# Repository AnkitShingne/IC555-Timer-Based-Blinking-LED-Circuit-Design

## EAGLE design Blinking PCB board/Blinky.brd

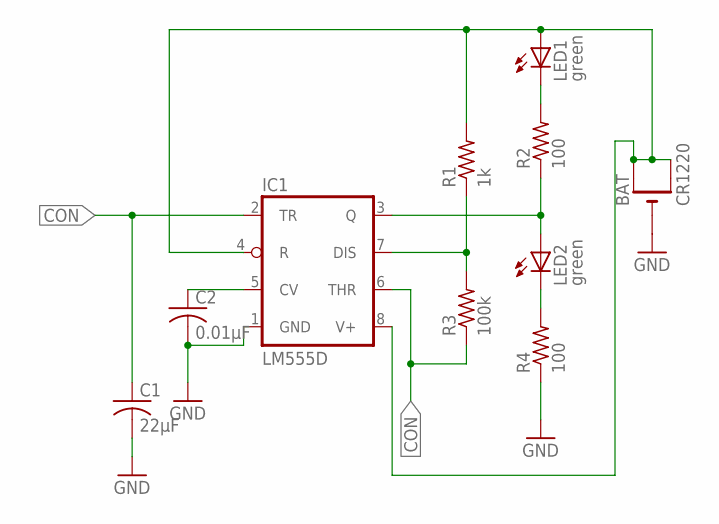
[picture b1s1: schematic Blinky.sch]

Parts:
BAT: CR1220; CR1220-SMD
C1: 22µF; C0805
C2: 0.01µF; C0805
IC1: LM555D; SO08
LED1, LED2: green; CHIPLED_0805
R1: 1k; R0805
R2, R4: 100; R0805
R3: 100k; R0805

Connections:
BAT: IC1.8 (V+)
CON: C1.1, IC1.2 (TR), IC1.6 (THR), R3.1
GND: BAT.-, C1.2, C2.2, IC1.1 (GND)
unnamed: LED1.C, R2.2
unnamed: IC1.3 (Q), LED2.A, R2.1
unnamed: LED2.C, R4.2
unnamed: IC1.7 (DIS), R1.1, R3.2
unnamed: BAT.+$1 (+), BAT.+$2 (+1), IC1.4 (R), LED1.A, R1.2
unnamed: C2.1, IC1.5 (CV)

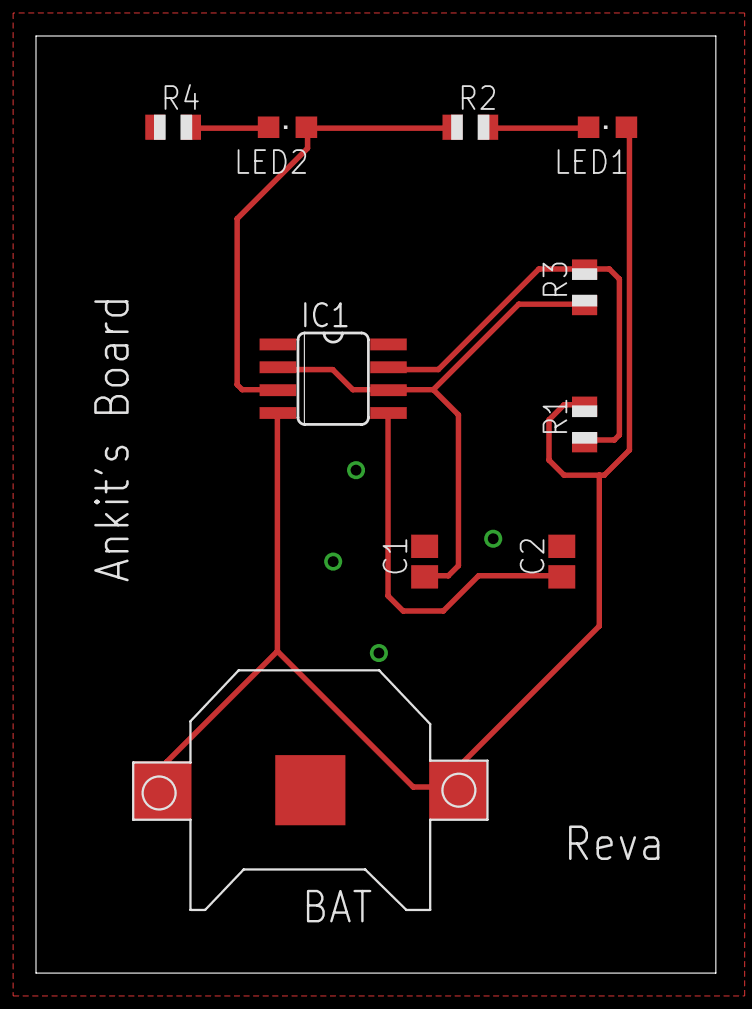
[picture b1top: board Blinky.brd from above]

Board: 2 copper layers, 37.8 x 52.1 mm, 10 parts (0 on the bottom side), 8 nets.
